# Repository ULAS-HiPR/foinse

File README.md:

# Foinse

Foinse is the power-source and monitoring node in [Ogma](https://sean-osullivan.com/projects/ogma/), the University of Limerick Aeronautics Society's modular avionics stack for high-powered rocketry.

## Role

- Generates and distributes the shared stack power rails.
- Measures battery and servo current.
- Reports power health over the 500 kbit/s CAN bus.
- Provides the stack's electrical entry point while each node performs its own local regulation.

## Repository

- `hardware/` - KiCad design and manufacturing outputs.
- `firmware/` - embedded firmware, power-path probes, and tests.

## Status

Rev 1 firmware and hardware bring-up continue on [`ogma/flight-hardening`](https://github.com/ULAS-HiPR/foinse/tree/ogma/flight-hardening). Release-candidate firmware builds and software tests pass, but hardware-in-the-loop validation is still underway. Foinse is not yet flight-proven.

## Manufacturing support

Rev 1 PCB fabrication was sponsored through [EasyEDA Education](https://easyeda.com/education) and manufactured by [JLCPCB](https://jlcpcb.com/). The board was designed in KiCad and imported into EasyEDA Pro for the sponsorship and manufacturing workflow.

## More information

See the [Ogma project write-up](https://sean-osullivan.com/projects/ogma/) for the complete stack, bring-up work, and current status.

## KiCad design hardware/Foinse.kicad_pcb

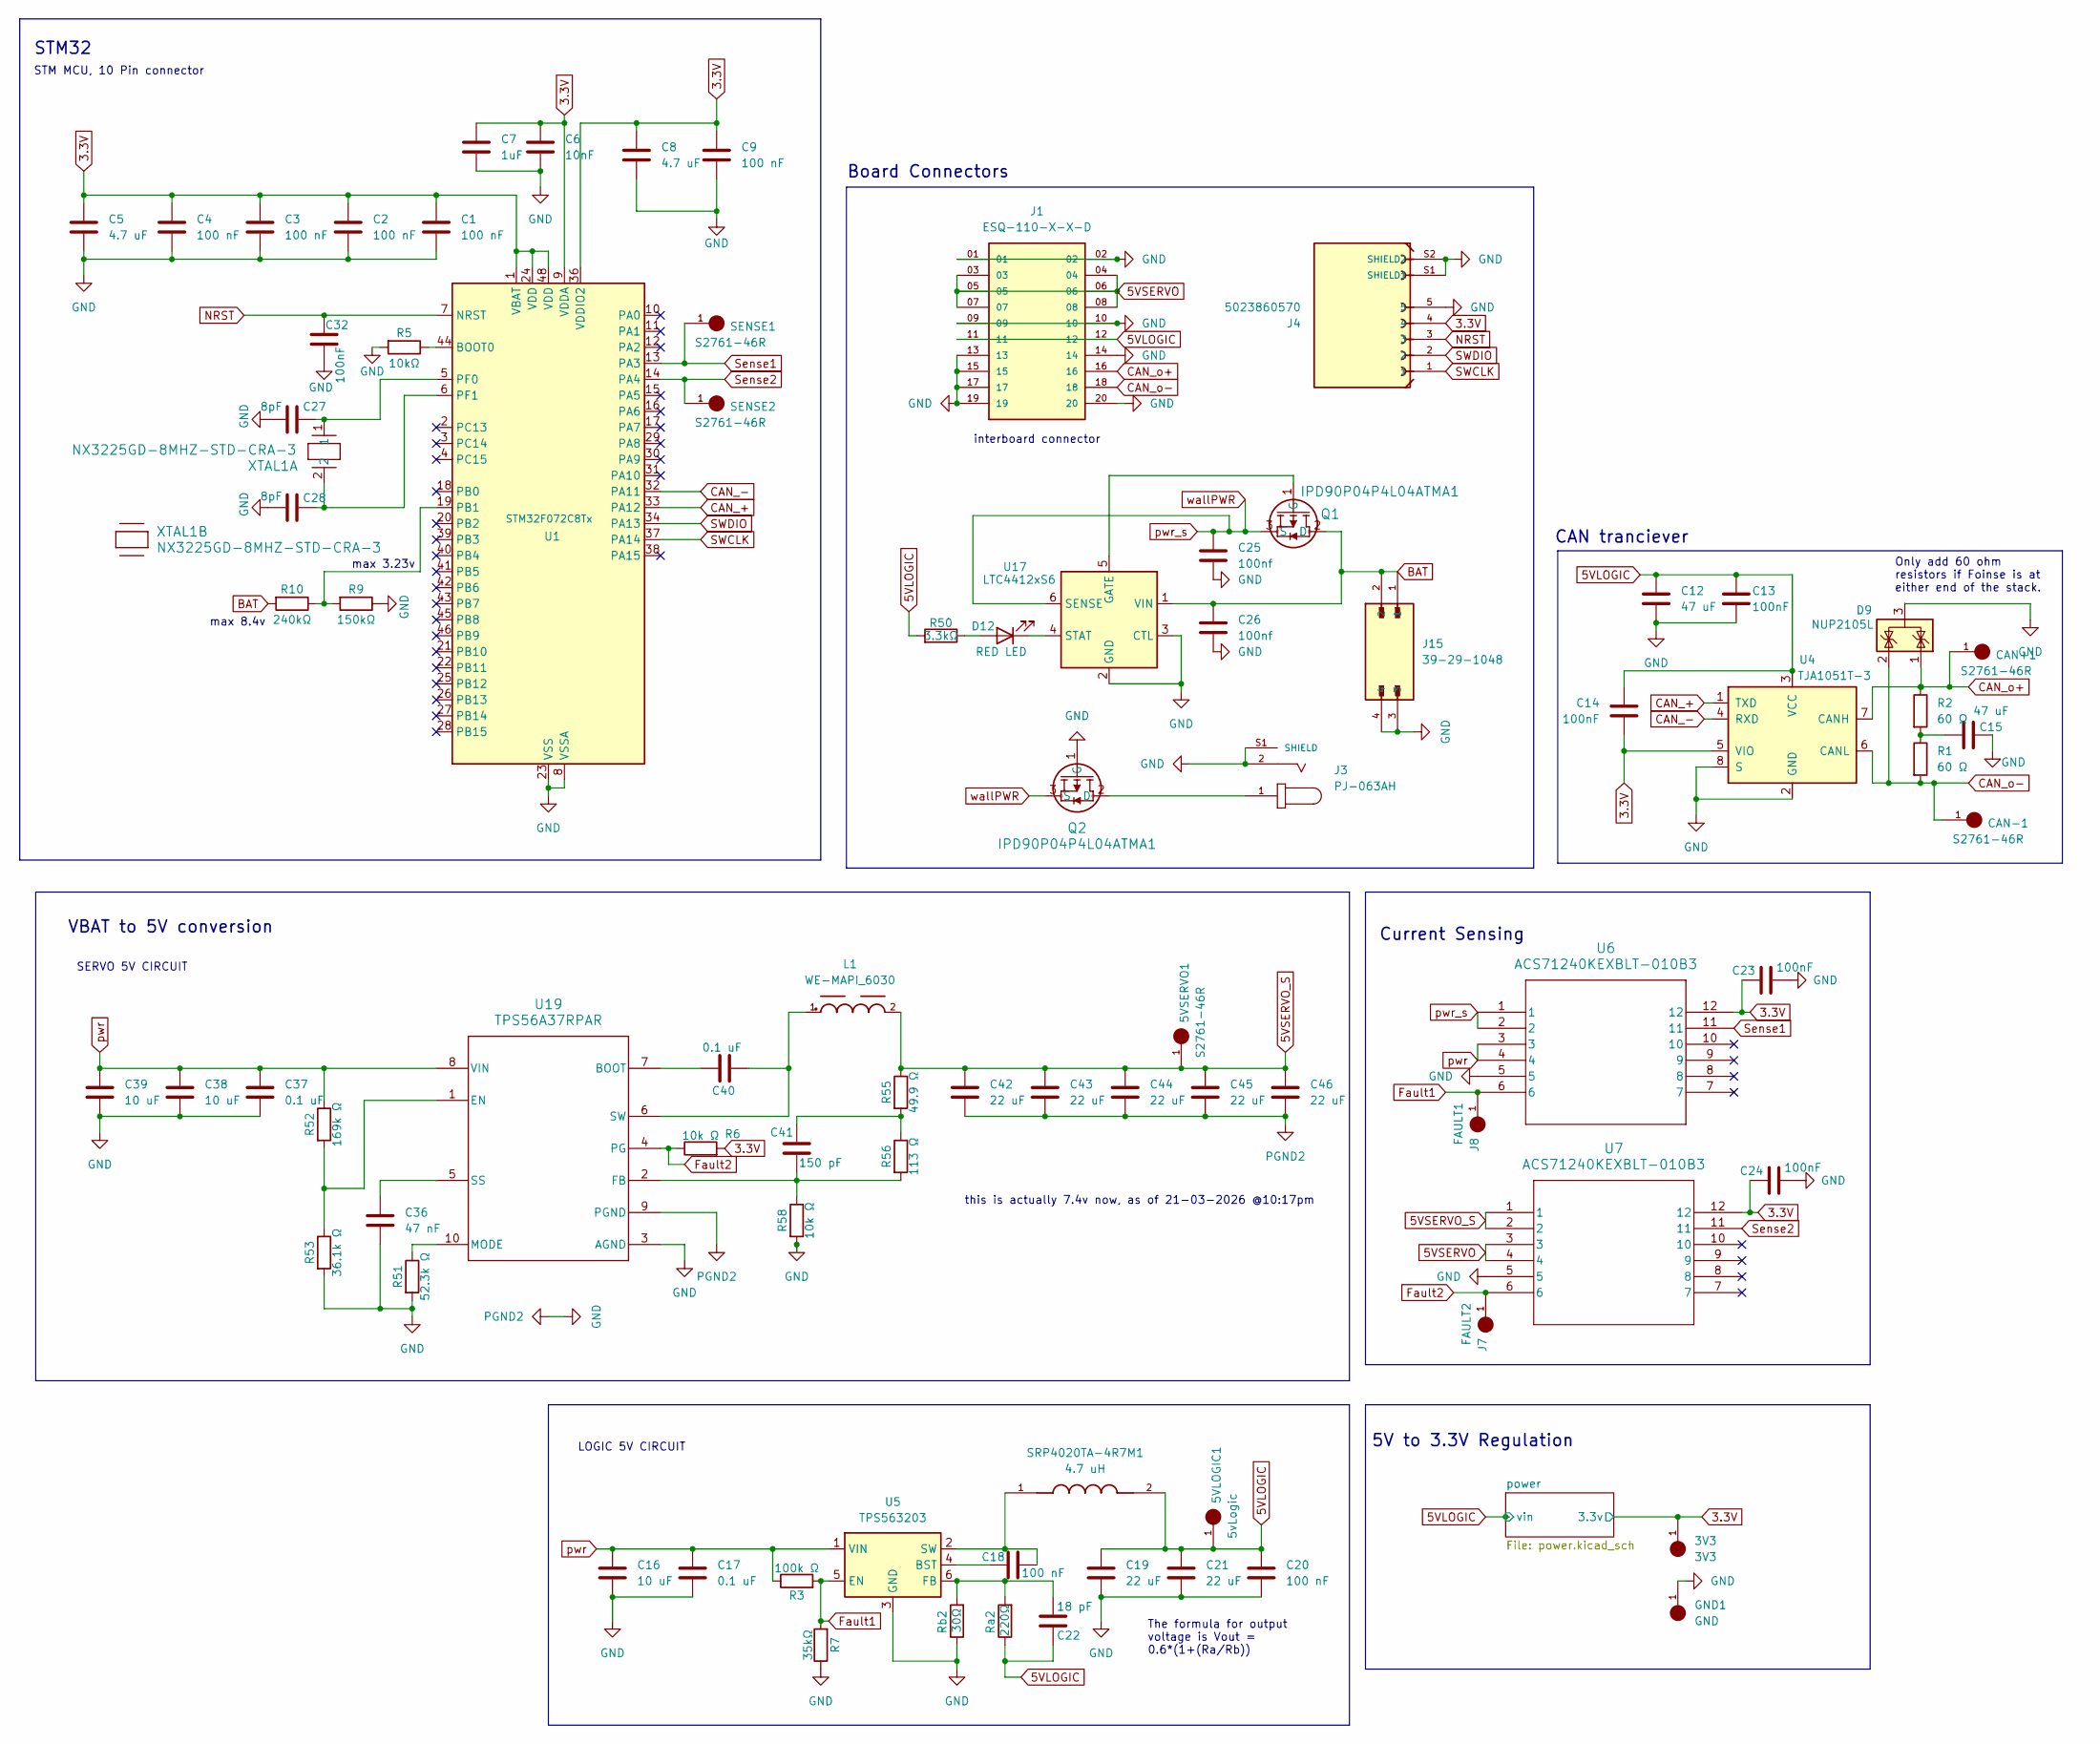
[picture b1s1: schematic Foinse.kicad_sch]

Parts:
3V3: 3V3; HARWIN_S2761-46R; PARTREV 1
5VLOGIC1: 5vLogic; HARWIN_S2761-46R; PARTREV 1
5VSERVO1: S2761-46R; HARWIN_S2761-46R; PARTREV 1
C1, C2, C3, C4, C9, C18, C20: 100 nF; C_0402_1005Metric
C5, C8: 4.7 uF; C_0402_1005Metric
C6: 10nF; C_0603_1608Metric
C7: 1uF; C_0402_1005Metric
C12, C15: 47 uF; C_0603_1608Metric
C13, C14, C23, C24, C32: 100nF; C_0402_1005Metric
C16, C38, C39: 10 uF; C_0603_1608Metric
C17, C37, C40: 0.1 uF; C_0402_1005Metric
C19, C21, C42, C43, C44, C45, C46: 22 uF; C_0603_1608Metric
C22: 18 pF; C_0402_1005Metric
C25, C26: 100nf; C_0402_1005Metric
C27, C28: 8pF; C_0402_1005Metric
C36: 47 nF; C_0402_1005Metric
C41: 150 pF; C_0402_1005Metric
CAN+1: S2761-46R; HARWIN_S2761-46R; PARTREV 1
CAN-1: S2761-46R; HARWIN_S2761-46R; PARTREV 1
D9: NUP2105L; SOT-23
D12: RED LED; LED_0402_1005Metric
GND1: GND; HARWIN_S2761-46R; PARTREV 1
J1: ESQ-110-X-X-D; SAMTEC_ESQ-110-14-G-D; PARTREV NA
J3: PJ-063AH; CUI_PJ-063AH; PARTREV 1.02
J4: 5023860570; MOLEX_5023860570; PARTREV F
J7: FAULT2; HARWIN_S2761-46R; PARTREV 1
J8: FAULT1; HARWIN_S2761-46R; PARTREV 1
J15: 39-29-1048; MOLEX_39-29-1048
L1: WE-MAPI_6030
Q1, Q2: IPD90P04P4L04ATMA1; PG-TO252-3-313_INF
R1, R2: 60 Ω; R_0402_1005Metric
R3: 100k Ω; R_0402_1005Metric
R5: 10kΩ; R_0402_1005Metric
R6, R58: 10k Ω; R_0402_1005Metric
R7: 35kΩ; R_0402_1005Metric
R9: 150kΩ; R_0402_1005Metric
R10: 240kΩ; R_0402_1005Metric
R50: 3.3kΩ; R_0402_1005Metric
R51: 52.3k Ω; R_0402_1005Metric
R52: 169k Ω; R_0402_1005Metric
R53: 36.1k Ω; R_0402_1005Metric
R55: 49.9 Ω; R_0402_1005Metric
R56: 113 Ω; R_0402_1005Metric
Ra2: 220Ω; R_0402_1005Metric
Rb2: 30Ω; R_0402_1005Metric
SENSE1, SENSE2: S2761-46R; HARWIN_S2761-46R; PARTREV 1
SRP4020TA-4R7M1: 4.7 uH; IND_SRP4020TA-4R7M
U1: STM32F072C8Tx; LQFP-48_7x7mm_P0.5mm
U4: TJA1051T-3; SOIC-8_3.9x4.9mm_P1.27mm
U5: TPS563203; SOT-563
U6, U7: ACS71240KEXBLT-010B3; QFN12_ACS711KEXLT-31AB-T_ALM
U17: LTC4412xS6; TSOT-23-6
U19: TPS56A37RPAR; RPA0010A-MFG
XTAL1: NX3225GD-8MHZ-STD-CRA-3; XTAL_NX3225GD-8MHZ-STD-CRA-3_NDK

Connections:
3.3V: 3V3.1, C1.1, C2.1, C3.1, C4.1, C5.1, C6.1, C7.1, C8.1, C9.1, C14.1, C23.2, C24.2, J4.4, R6.2, U1.1 (VBAT), U1.9 (VDDA), U1.24 (VDD), U1.36 (VDDIO2), U1.48 (VDD), U4.5 (VIO), U6.12, U7.12; also elsewhere on the board
5VLOGIC: 5VLOGIC1.1, C12.1, C13.1, C14.2, C19.1, C20.1, C21.1, C22.2, J1.11, J1.12, R50.2, Ra2.1, SRP4020TA-4R7M1.2, U4.3 (VCC); also elsewhere on the board
5VSERVO: J1.03, J1.04, J1.05, J1.06, J1.07, J1.08, U7.3, U7.4
5VSERVO_S: 5VSERVO1.1, C42.1, C43.1, C44.1, C45.1, C46.1, L1.2, R55.1, U7.1, U7.2; also elsewhere on the board
BAT: C26.1, J15.1, J15.2, Q1.2 (D), R10.2, U17.1 (VIN)
CAN_+: U1.33 (PA12), U4.1 (TXD)
CAN_-: U1.32 (PA11), U4.4 (RXD)
CAN_o+: CAN+1.1, D9.1 (K), J1.16, R2.1, U4.7 (CANH); also elsewhere on the board
CAN_o-: CAN-1.1, D9.2 (K), J1.18, R1.2, U4.6 (CANL); also elsewhere on the board
Fault1: J8.1, R3.2, R7.2, U5.5 (EN), U6.6; also elsewhere on the board
Fault2: J7.1, R6.1, U7.6, U19.4 (PG); also elsewhere on the board
GND: C1.2, C2.2, C3.2, C4.2, C5.2, C6.2, C7.2, C8.2, C9.2, C12.2, C13.2, C15.2, C16.2, C17.2, C19.2, C20.2, C21.2, C23.1, C24.1, C25.2, C26.2, C27.1, C28.2, C32.2, C36.2, C37.2, C38.2, C39.2, C42.2, C43.2, C44.2, C45.2, C46.2, D9.3 (A), GND1.1, J1.01, J1.02, J1.09, J1.10, J1.13, J1.14, J1.15, J1.17, J1.19, J1.20, J3.2, J3.S1 (SHIELD), J3.S2 (SHIELD), J4.5, J4.S1 (SHIELD1), J4.S2 (SHIELD2), J15.3, J15.4, Q2.1 (G), R5.2, R7.1, R9.1, R51.2, R53.2, R58.2, Rb2.1, U1.8 (VSSA), U1.23 (VSS), U1.35 (VSS), U1.47 (VSS), U4.2 (GND), U4.8 (S), U5.3 (GND), U6.5, U7.5, U17.2 (GND), U17.3 (CTL), U19.3 (AGND), U19.9 (PGND); also elsewhere on the board
NRST: C32.1, J4.3, U1.7 (NRST)
unnamed: C15.1, R1.1, R2.2
unnamed: C41.1, R55.2, R56.1
unnamed: D12.2 (A), R50.1
unnamed: D12.1 (K), U17.4 (STAT)
unnamed: Q1.1 (G), U17.5 (GATE)
unnamed: J3.1, Q2.2 (D)
unnamed: R5.1, U1.44 (BOOT0)
unnamed: R9.2, R10.1, U1.19 (PB1)
unnamed: C27.2, U1.5 (PF0), XTAL1.1
unnamed: C28.1, U1.6 (PF1), XTAL1.2
unnamed: C18.2, U5.4 (BST)
unnamed: C22.1, Ra2.2, Rb2.2, U5.6 (FB)
unnamed: C18.1, SRP4020TA-4R7M1.1, U5.2 (SW)
unnamed: C40.1, U19.7 (BOOT)
unnamed: R52.2, R53.1, U19.1 (EN)
unnamed: C41.2, R56.2, R58.1, U19.2 (FB)
unnamed: R51.1, U19.10 (MODE)
unnamed: C36.1, U19.5 (SS)
unnamed: C40.2, L1.1, U19.6 (SW)
SWCLK: J4.1, U1.37 (PA14)
SWDIO: J4.2, U1.34 (PA13)
Sense1: SENSE1.1, U1.13 (PA3), U6.11; also elsewhere on the board
Sense2: SENSE2.1, U1.14 (PA4), U7.11; also elsewhere on the board
pwr: C16.1, C17.1, C37.1, C38.1, C39.1, R3.1, R52.1, U5.1 (VIN), U6.3, U6.4, U19.8 (VIN)
pwr_s: C25.1, Q1.3 (S), Q2.3 (S), U6.1, U6.2, U17.6 (SENSE)

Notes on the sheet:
max 3.23v
Board Connectors
5V to 3.3V Regulation
Current Sensing
this is actually 7.4v now, as of 21-03-2026 @10:17pm
interboard connector
STM MCU, 10 Pin connector
STM32
max 8.4v
VBAT to 5V conversion
CAN tranciever
LOGIC 5V CIRCUIT
SERVO 5V CIRCUIT
Only add 60 ohm resistors if Foinse is at either end of the stack.
The formula for output voltage is Vout = 0.6*(1+(Ra/Rb))

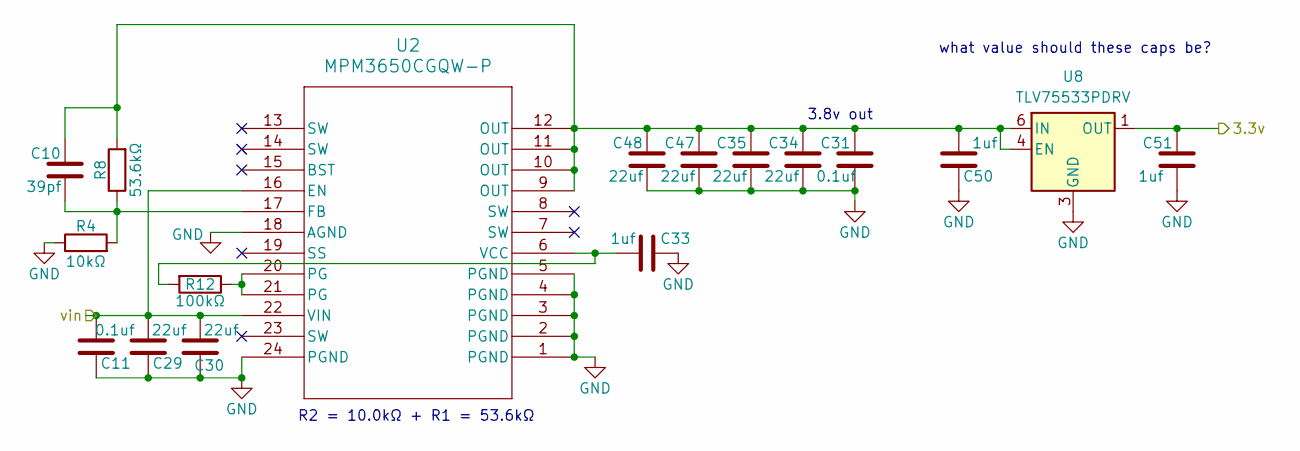
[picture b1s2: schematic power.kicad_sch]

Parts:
C10: 39pf; C_0402_1005Metric
C11, C31: 0.1uf; C_0402_1005Metric
C29, C30, C34, C35, C47, C48: 22uf; C_0603_1608Metric
C33, C50, C51: 1uf; C_0402_1005Metric
R4: 10kΩ; R_0402_1005Metric
R8: 53.6kΩ; R_0402_1005Metric
R12: 100kΩ; R_0402_1005Metric
U2: MPM3650CGQW-P; QFN-24_MPM3650_MNP
U8: TLV75533PDRV; WSON-6-1EP_2x2mm_P0.65mm_EP1x1.6mm

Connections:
3.3V: C51.1, U8.1 (OUT); also elsewhere on the board
5VLOGIC: C11.2, C29.2, C30.2, U2.16 (EN), U2.22 (VIN); also elsewhere on the board
GND: C11.1, C29.1, C30.1, C31.2, C33.1, C34.2, C35.2, C47.2, C48.2, C50.1, C51.2, R4.1, U2.1 (PGND), U2.2 (PGND), U2.3 (PGND), U2.4 (PGND), U2.5 (PGND), U2.18 (AGND), U2.24 (PGND), U8.3 (GND), U8.7 (GND); also elsewhere on the board
unnamed: R12.1, U2.20 (PG), U2.21 (PG)
unnamed: C10.2, R4.2, R8.1, U2.17 (FB)
unnamed: C33.2, R12.2, U2.6 (VCC)
unnamed: C10.1, C31.1, C34.1, C35.1, C47.1, C48.1, C50.2, R8.2, U2.9 (OUT), U2.10 (OUT), U2.11 (OUT), U2.12 (OUT), U8.4 (EN), U8.6 (IN)

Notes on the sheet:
R2 = 10.0kΩ + R1 = 53.6kΩ
3.8v out
what value should these caps be?

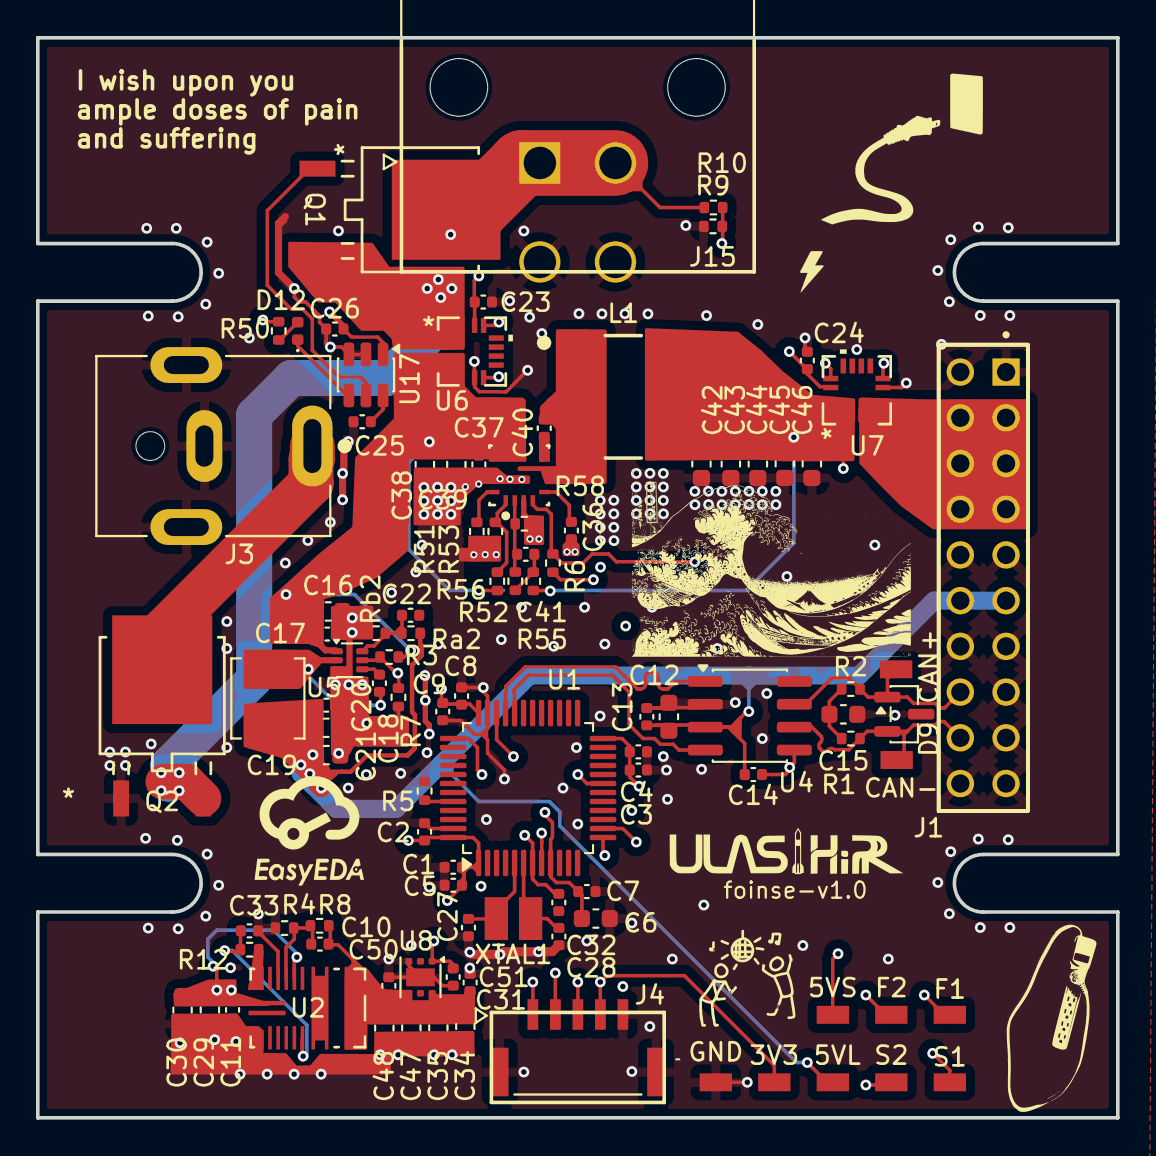
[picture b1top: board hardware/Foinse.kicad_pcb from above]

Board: 6 copper layers, 60.0 x 60.0 mm, 100 parts (0 on the bottom side), 42 nets.

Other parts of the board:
5VL: 5vLogic; HARWIN_S2761-46R
5VS: S2761-46R; HARWIN_S2761-46R
CAN+: S2761-46R; HARWIN_S2761-46R
CAN-: S2761-46R; HARWIN_S2761-46R
F1: FAULT1; HARWIN_S2761-46R
F2: FAULT2; HARWIN_S2761-46R
GND: GND; HARWIN_S2761-46R
S1, S2: S2761-46R; HARWIN_S2761-46R

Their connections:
5VLOGIC: 5VL.1; also elsewhere on the board
5VSERVO_S: 5VS.1; also elsewhere on the board
CAN_o+: CAN+.1; also elsewhere on the board
CAN_o-: CAN-.1; also elsewhere on the board
Fault1: F1.1; also elsewhere on the board
Fault2: F2.1; also elsewhere on the board
GND: GND.1; also elsewhere on the board
Sense1: S1.1; also elsewhere on the board
Sense2: S2.1; also elsewhere on the board

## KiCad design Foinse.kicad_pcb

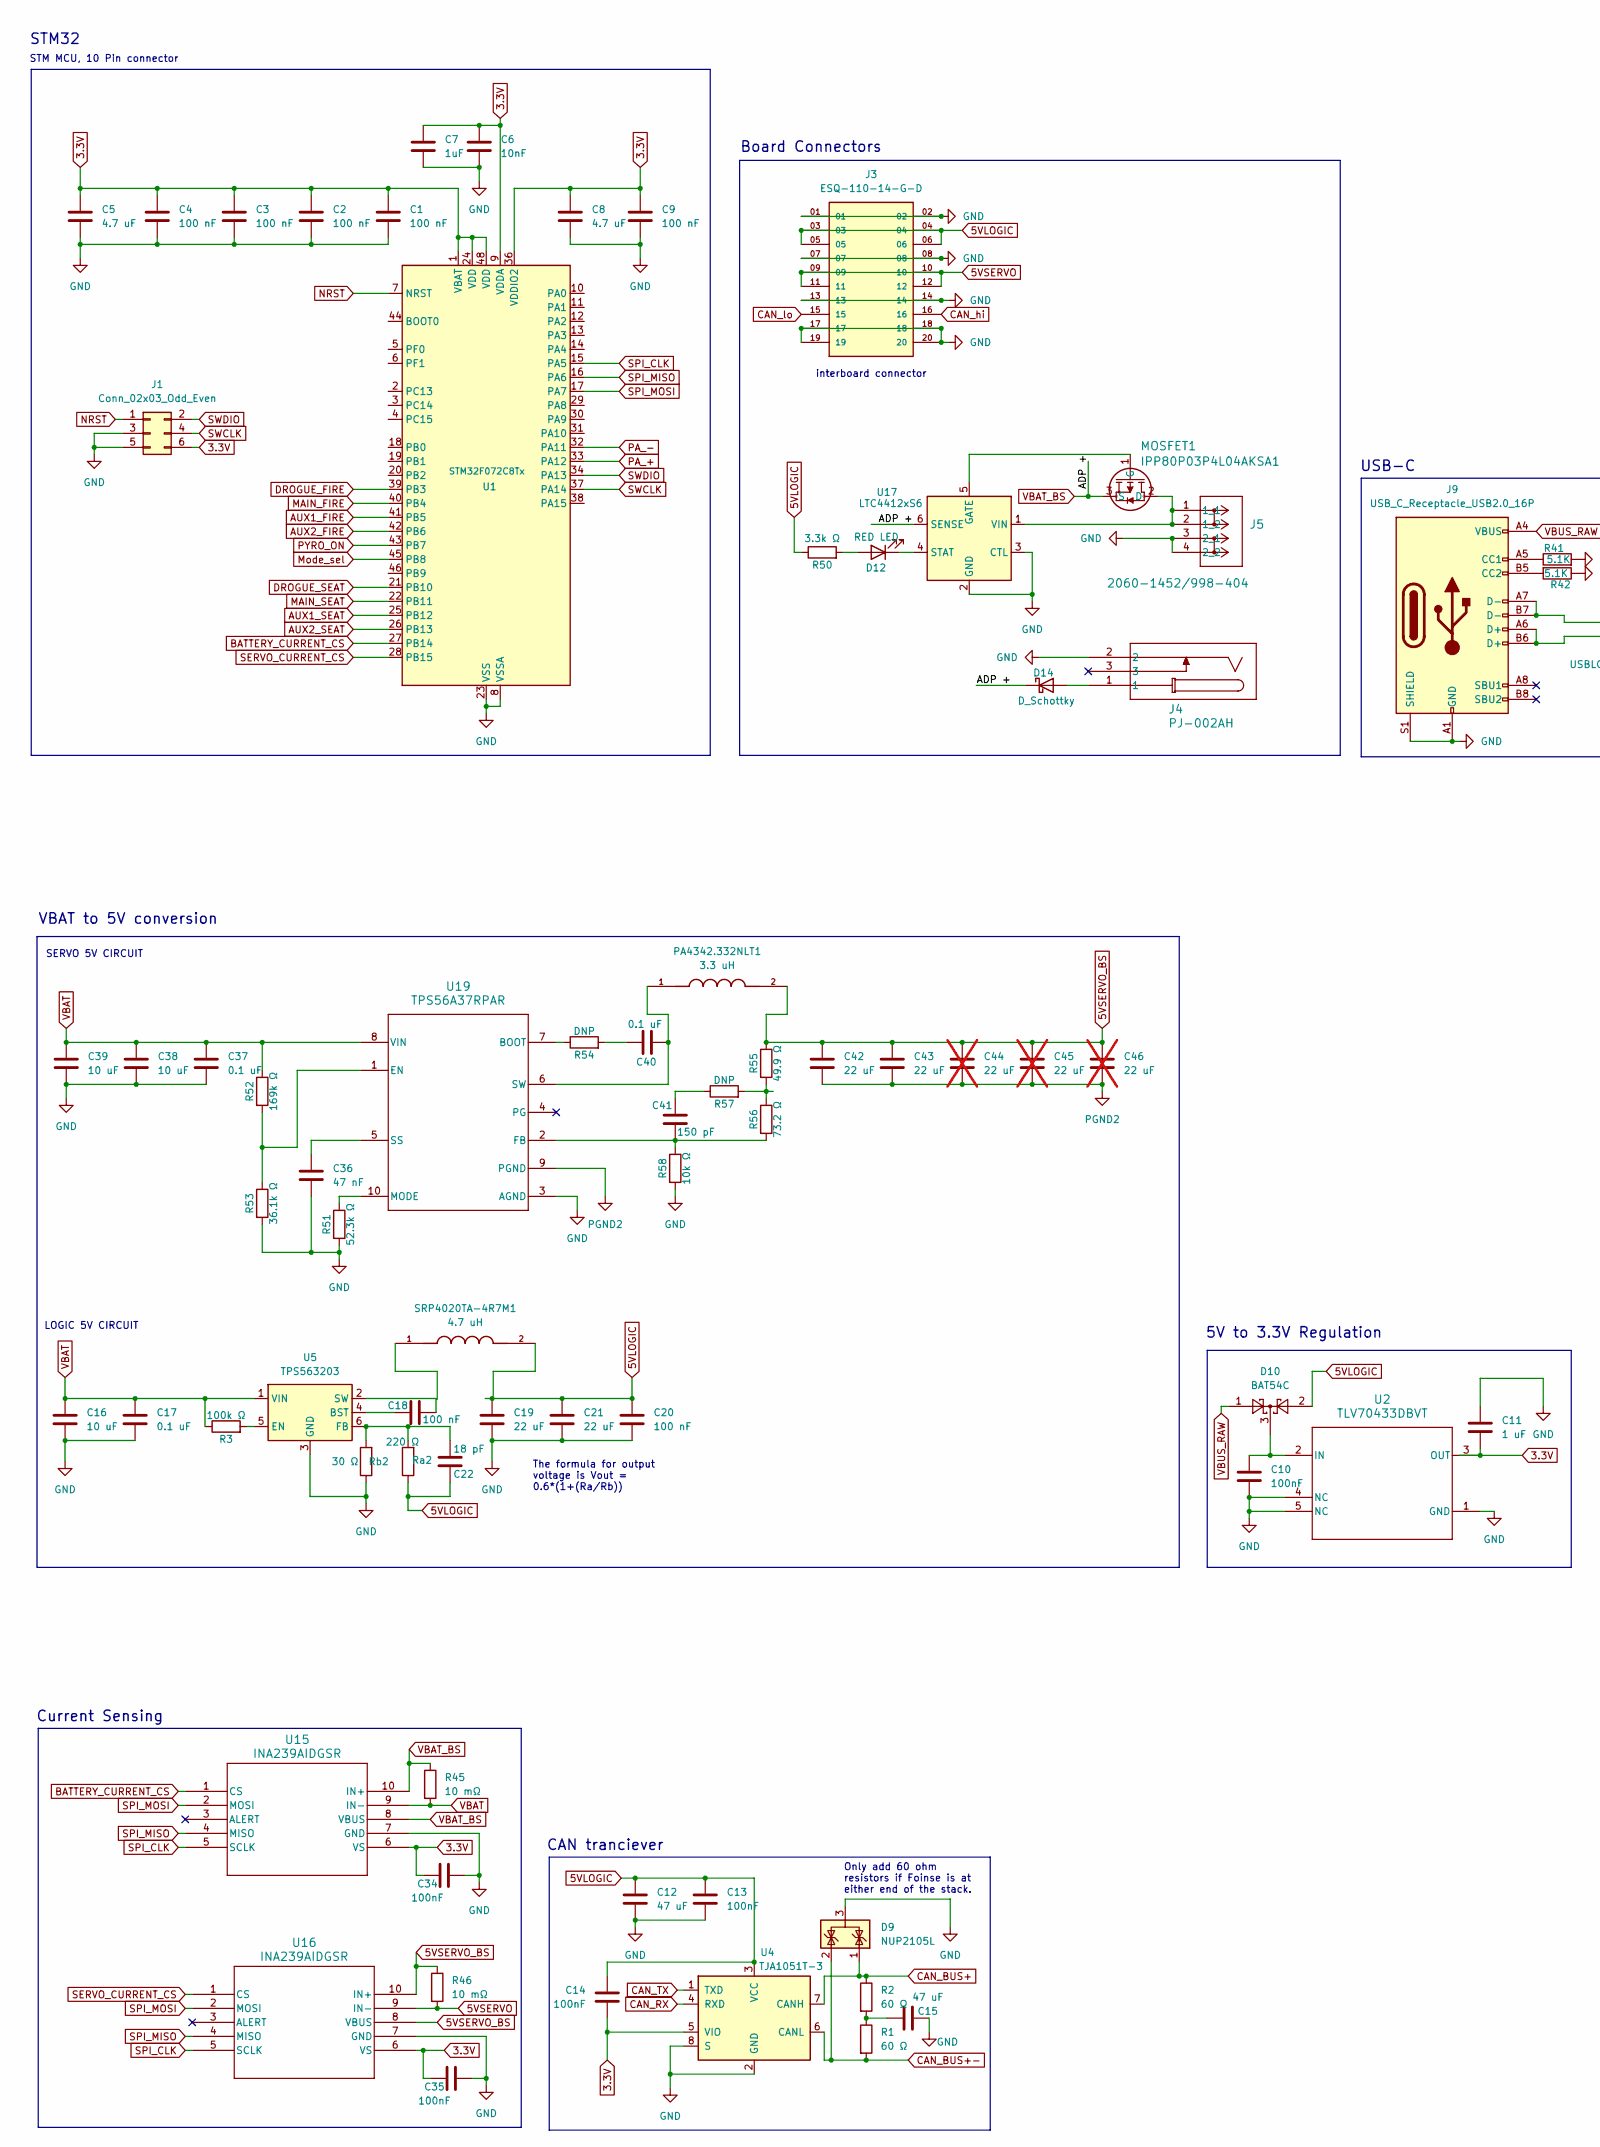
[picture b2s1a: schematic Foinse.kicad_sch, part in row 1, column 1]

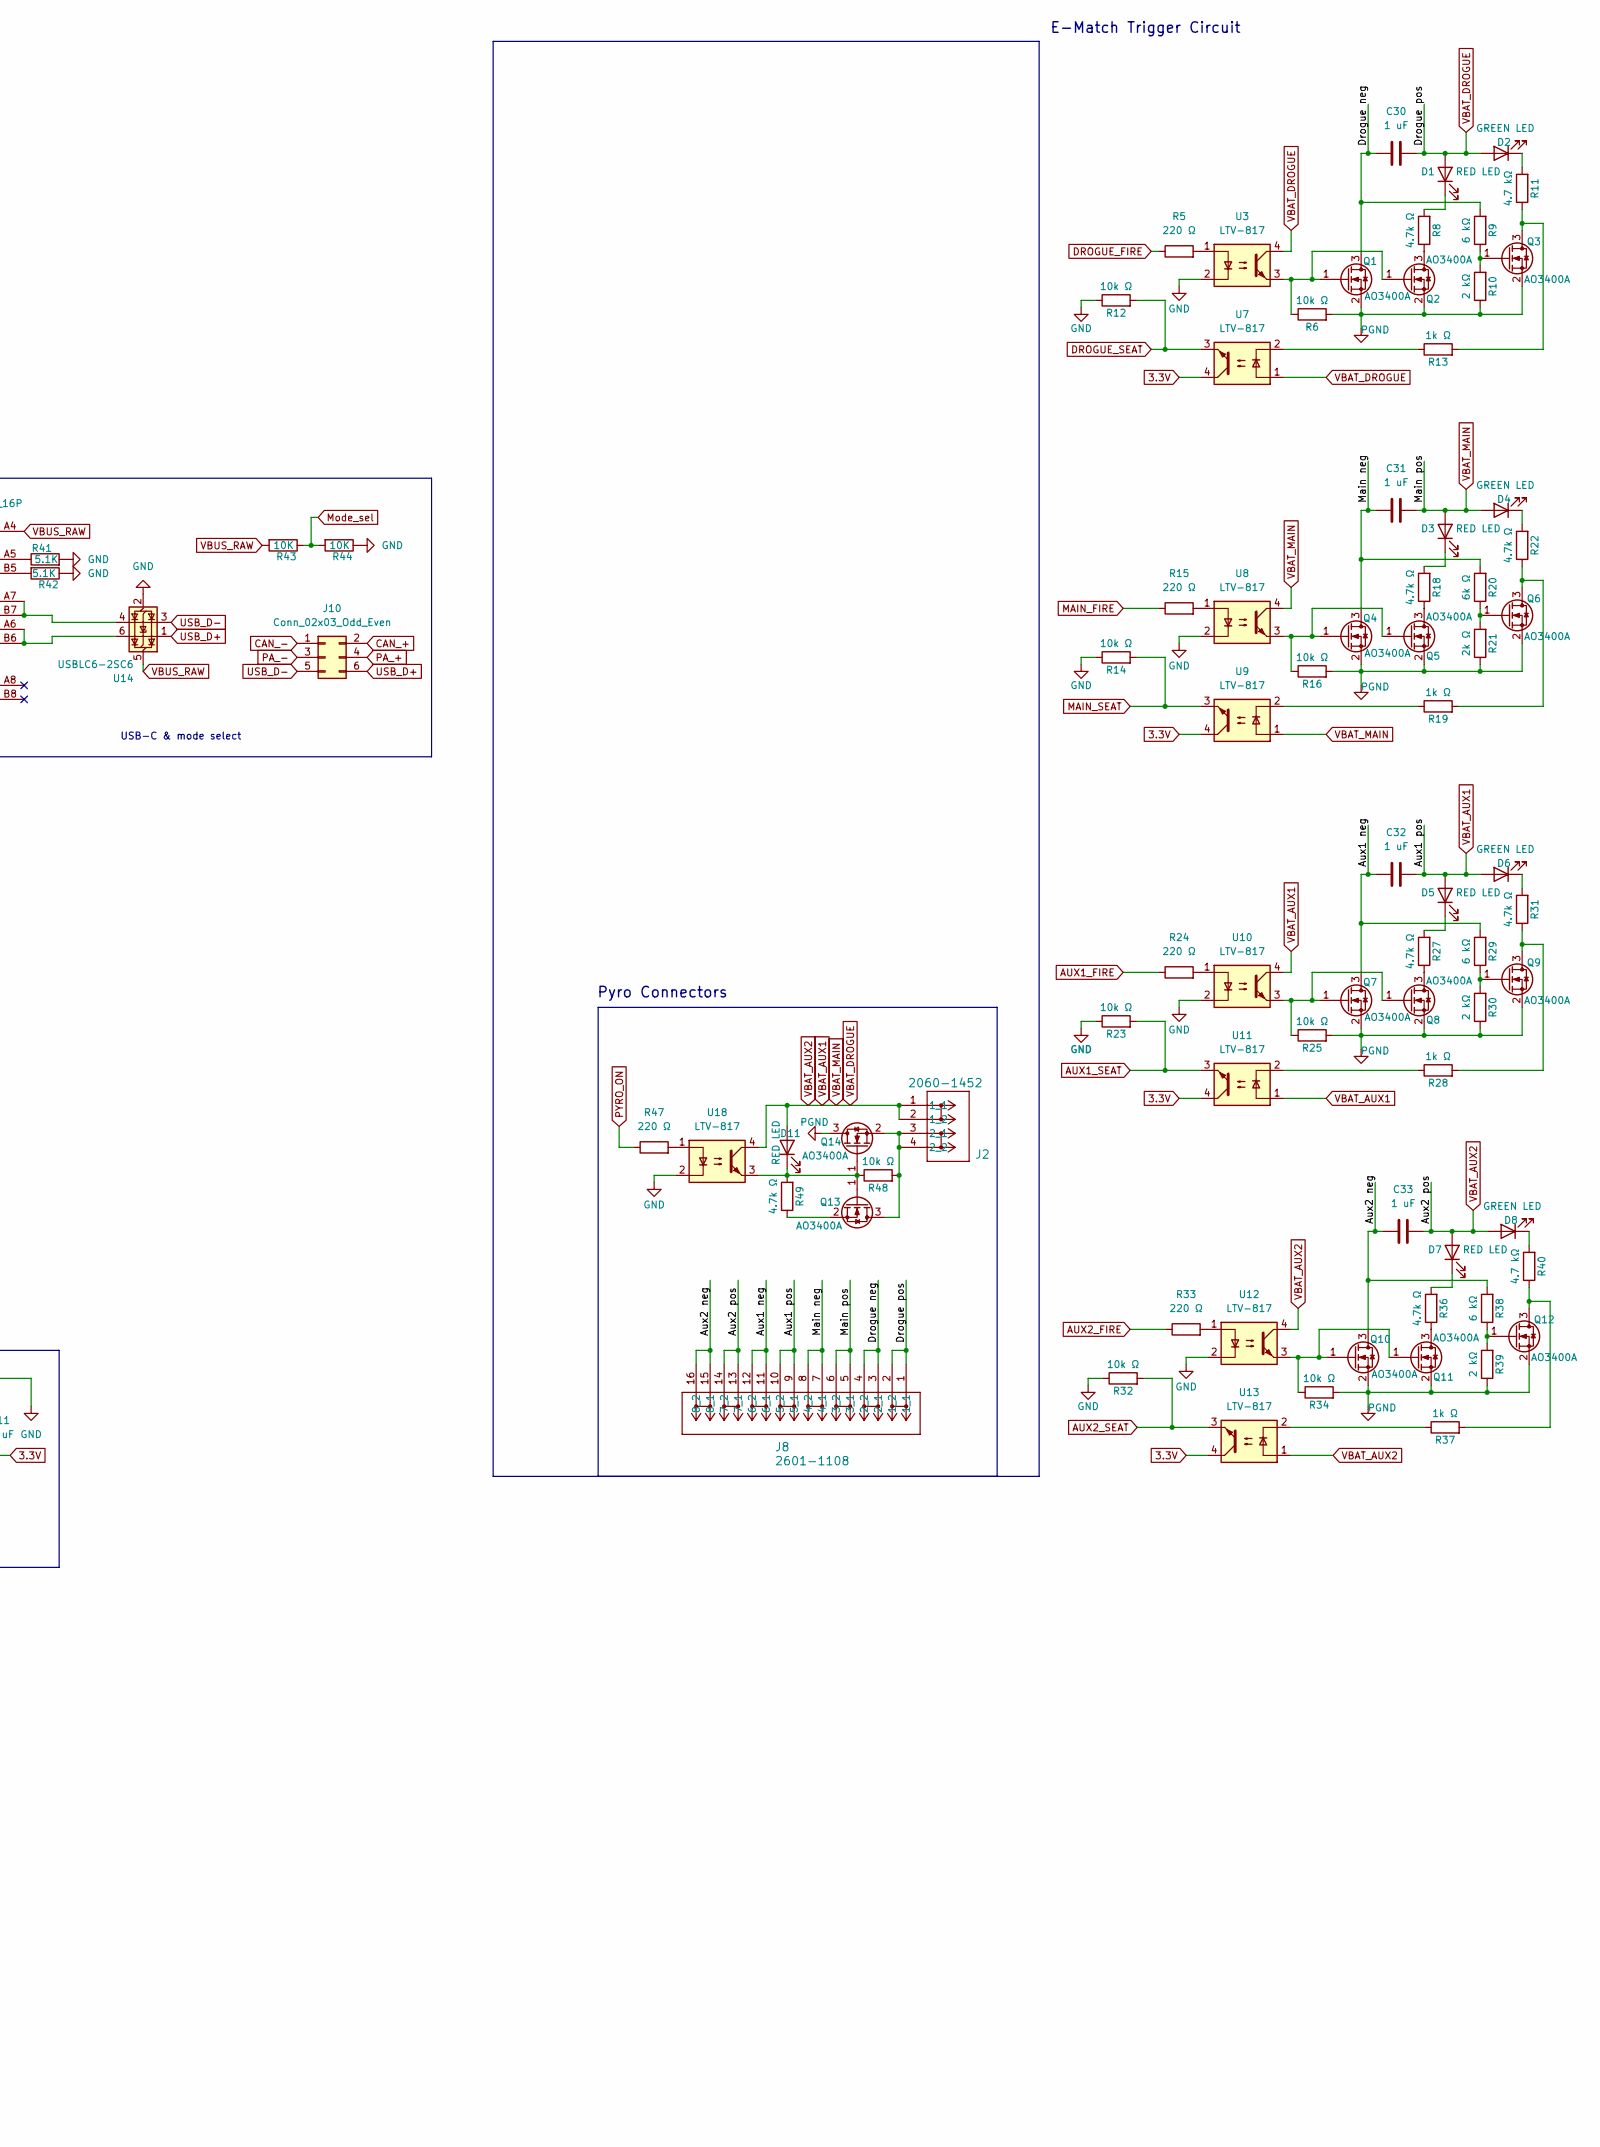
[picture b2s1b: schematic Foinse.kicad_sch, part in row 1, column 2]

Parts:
C1, C2, C3, C4, C9, C18, C20: 100 nF; C_0402_1005Metric
C5, C8: 4.7 uF; C_0402_1005Metric
C6: 10nF; C_0402_1005Metric
C7: 1uF; C_0402_1005Metric
C10, C13, C14, C34, C35: 100nF; C_0402_1005Metric
C11, C30, C31, C32, C33: 1 uF; C_0402_1005Metric
C12, C15: 47 uF; C_0402_1005Metric
C16, C38, C39: 10 uF; C_0402_1005Metric
C17, C37, C40: 0.1 uF; C_0402_1005Metric
C19, C21, C42, C43: 22 uF; C_0402_1005Metric
C22: 18 pF; C_0402_1005Metric
C36: 47 nF; C_0402_1005Metric
C41: 150 pF; C_0402_1005Metric
C44, C45, C46: 22 uF; C_0402_1005Metric; not fitted
D1, D3, D5, D7, D11, D12: RED LED; LED_0402_1005Metric
D2, D4, D6, D8: GREEN LED; LED_0402_1005Metric
D9: NUP2105L; SOT-23
D10: BAT54C; SOT-23
D14: D_Schottky; TO-220-3_Vertical
J1, J10: Conn_02x03_Odd_Even; PinHeader_2x03_P1.00mm_Vertical
J2: 2060-1452; WAG
J3: ESQ-110-14-G-D; SAMTEC_ESQ-110-14-G-D; PARTREV NA
J4: PJ-002AH; PJ-002AH_CUD
J5: 2060-1452/998-404; WAG
J8: 2601-1108; CONN8_2601-1108_WAG
J9: USB_C_Receptacle_USB2.0_16P; USB_C_Receptacle_G-Switch_GT-USB-7010ASV
MOSFET1: IPP80P03P4L04AKSA1
PA4342.332NLT1: 3.3 uH; IND_PA4342.332NLT; PARTREV P769.L (06/20)
Q1, Q2, Q3, Q4, Q5, Q6, Q7, Q8, Q9, Q10, Q11, Q12, Q13, Q14: AO3400A; SOT-23
R1, R2: 60 Ω; R_0402_1005Metric
R3: 100k Ω; R_0402_1005Metric
R5, R15, R24, R33, R47: 220 Ω; R_0402_1005Metric
R6, R12, R14, R16, R23, R25, R32, R34, R48, R58: 10k Ω; R_0402_1005Metric
R8, R18, R22, R27, R31, R36, R49: 4.7k Ω; R_0402_1005Metric
R9, R29, R38: 6 kΩ; R_0402_1005Metric
R10, R30, R39: 2 kΩ; R_0402_1005Metric
R11, R40: 4.7 kΩ; R_0402_1005Metric
R13, R19, R28, R37: 1k Ω; R_0402_1005Metric
R20: 6k Ω; R_0402_1005Metric
R21: 2k Ω; R_0402_1005Metric
R41, R42: 5.1K; R_0402_1005Metric
R43, R44: 10K; R_0402_1005Metric
R45, R46: 10 mΩ; R_0402_1005Metric
R50: 3.3k Ω; R_0402_1005Metric
R51: 52.3k Ω; R_0402_1005Metric
R52: 169k Ω; R_0402_1005Metric
R53: 36.1k Ω; R_0402_1005Metric
R54, R57: DNP; R_0402_1005Metric
R55: 49.9 Ω; R_0402_1005Metric
R56: 73.2 Ω; R_0402_1005Metric
Ra2: 220 Ω; R_0402_1005Metric
Rb2: 30 Ω; R_0402_1005Metric
SRP4020TA-4R7M1: 4.7 uH; IND_SRP4020TA-4R7M
U1: STM32F072C8Tx; LQFP-48_7x7mm_P0.5mm
U2: TLV70433DBVT; DBV0005A_N
U3, U7, U8, U9, U10, U11, U12, U13, U18: LTV-817; SO4_TOS
U4: TJA1051T-3; SOIC-8_3.9x4.9mm_P1.27mm
U5: TPS563203; SOT-563
U14: USBLC6-2SC6; SOT-23-6
U15, U16: INA239AIDGSR; VSSOP_9AIDGST_TEX
U17: LTC4412xS6; TSOT-23-6
U19: TPS56A37RPAR; RPA0010A-MFG

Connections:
3.3V: C1.1, C2.1, C3.1, C4.1, C5.1, C6.1, C7.1, C8.1, C9.1, C11.2, C14.1, C34.1, C35.1, J1.6, U1.1 (VBAT), U1.9 (VDDA), U1.24 (VDD), U1.36 (VDDIO2), U1.48 (VDD), U2.3 (OUT), U4.5 (VIO), U7.4, U9.4, U11.4, U13.4, U15.6 (VS), U16.6 (VS)
5VLOGIC: C12.1, C13.1, C14.2, C19.1, C20.1, C21.1, C22.2, D10.2, J3.03, J3.04, J3.05, J3.06, R50.1, Ra2.1, U4.3 (VCC)
5VSERVO: J3.09, J3.10, J3.11, J3.12, R46.2, U16.9 (IN-)
5VSERVO_BS: C42.1, C43.1, C44.1, C45.1, C46.1, PA4342.332NLT1.2, R46.1, R55.1, U16.8 (VBUS), U16.10 (IN+)
/Aux1 neg: C32.2, J8.11 (6_1), J8.12 (6_2), Q7.3 (D), R29.2
/Aux2 neg: C33.2, J8.15 (8_1), J8.16 (8_2), Q10.3 (D), R38.2
/Drogue neg: C30.2, J8.3 (2_1), J8.4 (2_2), Q1.3 (D), R9.2
/Main neg: C31.2, J8.7 (4_1), J8.8 (4_2), Q4.3 (D), R20.2
AUX1_FIRE: R24.1, U1.41 (PB5)
AUX1_SEAT: R23.2, U1.25 (PB12), U11.3
AUX2_FIRE: R33.1, U1.42 (PB6)
AUX2_SEAT: R32.2, U1.26 (PB13), U13.3
BATTERY_CURRENT_CS: U1.27 (PB14), U15.1 (CS)
CAN_+: J10.2
CAN_-: J10.1
CAN_BUS+: D9.1 (K), R2.1, U4.7 (CANH)
CAN_BUS+-: D9.2 (K), R1.2, U4.6 (CANL)
CAN_RX: U4.4 (RXD)
CAN_TX: U4.1 (TXD)
CAN_hi: J3.16
CAN_lo: J3.15
DROGUE_FIRE: R5.1, U1.39 (PB3)
DROGUE_SEAT: R12.2, U1.21 (PB10), U7.3
GND: C1.2, C2.2, C3.2, C4.2, C5.2, C6.2, C7.2, C8.2, C9.2, C10.2, C11.1, C12.2, C13.2, C15.2, C16.2, C17.2, C19.2, C20.2, C21.2, C34.2, C35.2, C36.2, C37.2, C38.2, C39.2, D9.3 (A), J1.3, J1.5, J3.01, J3.02, J3.07, J3.08, J3.13, J3.14, J3.17, J3.18, J3.19, J3.20, J4.2, J5.3 (2_1), J5.4 (2_2), J9.A1 (GND), J9.A12 (GND), J9.B1 (GND), J9.B12 (GND), J9.S1 (SHIELD), R12.1, R14.1, R23.1, R32.1, R41.2, R42.1, R44.1, R51.2, R53.2, R58.2, Rb2.1, U1.8 (VSSA), U1.23 (VSS), U1.35 (VSS), U1.47 (VSS), U2.1 (GND), U2.4 (NC), U2.5 (NC), U3.2, U4.2 (GND), U4.8 (S), U5.3 (GND), U8.2, U10.2, U12.2, U14.2 (GND), U15.7 (GND), U16.7 (GND), U17.2 (GND), U17.3 (CTL), U18.2, U19.3 (AGND)
MAIN_FIRE: R15.1, U1.40 (PB4)
MAIN_SEAT: R14.2, U1.22 (PB11), U9.3
Mode_sel: R43.1, R44.2, U1.45 (PB8)
NRST: J1.1, U1.7 (NRST)
unnamed: C15.1, R1.1, R2.2
unnamed: C40.1, R54.2
unnamed: C41.1, R57.1
unnamed: D1.1 (K), R8.2
unnamed: D2.1 (K), R11.2
unnamed: D3.1 (K), R18.2
unnamed: D4.1 (K), R22.2
unnamed: D5.1 (K), R27.2
unnamed: D6.1 (K), R31.2
unnamed: D7.1 (K), R36.2
unnamed: D8.1 (K), R40.2
unnamed: D11.1 (K), Q13.1 (G), Q14.1 (G), R48.1, R49.2, U18.3
unnamed: D12.2 (A), R50.2
unnamed: D12.1 (K), U17.4 (STAT)
unnamed: D14.2 (A), J4.1
unnamed: J2.3 (2_1), J2.4 (2_2), Q13.3 (D), Q14.2 (S), R48.2
unnamed: J5.1 (1_1), J5.2 (1_2), MOSFET1.2 (D), U17.1 (VIN)
unnamed: J9.A5 (CC1), R41.1
unnamed: J9.B5 (CC2), R42.2
unnamed: J9.A6 (D+), J9.B6 (D+), U14.6 (I/O1)
unnamed: J9.A7 (D-), J9.B7 (D-), U14.4 (I/O2)
unnamed: MOSFET1.1 (G), U17.5 (GATE)
unnamed: Q1.1 (G), Q2.1 (G), R6.1, U3.3
unnamed: Q2.3 (D), R8.1
unnamed: Q3.3 (D), R11.1, R13.2
unnamed: Q3.1 (G), R9.1, R10.2
unnamed: Q4.1 (G), Q5.1 (G), R16.1, U8.3
unnamed: Q5.3 (D), R18.1
unnamed: Q6.3 (D), R19.2, R22.1
unnamed: Q6.1 (G), R20.1, R21.2
unnamed: Q7.1 (G), Q8.1 (G), R25.1, U10.3
unnamed: Q8.3 (D), R27.1
unnamed: Q9.3 (D), R28.2, R31.1
unnamed: Q9.1 (G), R29.1, R30.2
unnamed: Q10.1 (G), Q11.1 (G), R34.1, U12.3
unnamed: Q11.3 (D), R36.1
unnamed: Q12.3 (D), R37.2, R40.1
unnamed: Q12.1 (G), R38.1, R39.2
unnamed: Q13.2 (S), R49.1
unnamed: R5.2, U3.1
unnamed: R13.1, U7.2
unnamed: R15.2, U8.1
unnamed: R19.1, U9.2
unnamed: R24.2, U10.1
unnamed: R28.1, U11.2
unnamed: R33.2, U12.1
unnamed: R37.1, U13.2
unnamed: R47.2, U18.1
unnamed: R55.2, R56.1, R57.2
unnamed: C10.1, D10.3, U2.2 (IN)
unnamed: C18.2, U5.4 (BST)
unnamed: R3.2, U5.5 (EN)
unnamed: C22.1, Ra2.2, Rb2.2, U5.6 (FB)
unnamed: C18.1, U5.2 (SW)
unnamed: R54.1, U19.7 (BOOT)
unnamed: R52.2, R53.1, U19.1 (EN)
unnamed: C41.2, R56.2, R58.1, U19.2 (FB)
unnamed: R51.1, U19.10 (MODE)
unnamed: C36.1, U19.5 (SS)
unnamed: C40.2, PA4342.332NLT1.1, U19.6 (SW)
PA_+: J10.4, U1.33 (PA12)
PA_-: J10.3, U1.32 (PA11)
PGND: Q1.2 (S), Q2.2 (S), Q3.2 (S), Q4.2 (S), Q5.2 (S), Q6.2 (S), Q7.2 (S), Q8.2 (S), Q9.2 (S), Q10.2 (S), Q11.2 (S), Q12.2 (S), Q14.3 (D), R6.2, R10.1, R16.2, R21.1, R25.2, R30.1, R34.2, R39.1
PGND2: C42.2, C43.2, C44.2, C45.2, C46.2, U19.9 (PGND)
PYRO_ON: R47.1, U1.43 (PB7)
SERVO_CURRENT_CS: U1.28 (PB15), U16.1 (CS)
SPI_CLK: U1.15 (PA5), U15.5 (SCLK), U16.5 (SCLK)
SPI_MISO: U1.16 (PA6), U15.4 (MISO), U16.4 (MISO)
SPI_MOSI: U1.17 (PA7), U15.2 (MOSI), U16.2 (MOSI)
SWCLK: J1.4, U1.37 (PA14)
SWDIO: J1.2, U1.34 (PA13)
USB_D+: J10.6, U14.1 (I/O1)
USB_D-: J10.5, U14.3 (I/O2)
VBAT: C16.1, C17.1, C37.1, C38.1, C39.1, R3.1, R45.2, R52.1, U5.1 (VIN), U15.9 (IN-), U19.8 (VIN)
VBAT_AUX1: C30.1, C31.1, C32.1, C33.1, D1.2 (A), D2.2 (A), D3.2 (A), D4.2 (A), D5.2 (A), D6.2 (A), D7.2 (A), D8.2 (A), D11.2 (A), J2.1 (1_1), J2.2 (1_2), J8.1 (1_1), J8.2 (1_2), J8.5 (3_1), J8.6 (3_2), J8.9 (5_1), J8.10 (5_2), J8.13 (7_1), J8.14 (7_2), U3.4, U7.1, U8.4, U9.1, U10.4, U11.1, U12.4, U13.1, U18.4
VBAT_BS: D14.1 (K), MOSFET1.3 (S), R45.1, U15.8 (VBUS), U15.10 (IN+), U17.6 (SENSE)
VBUS_RAW: D10.1, J9.A4 (VBUS), J9.A9 (VBUS), J9.B4 (VBUS), J9.B9 (VBUS), R43.2, U14.5 (VBUS)

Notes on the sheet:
Board Connectors
Pyro Connectors
E-Match Trigger Circuit
interboard connector
5V to 3.3V Regulation
Current Sensing
STM MCU, 10 Pin connector
STM32
USB-C & mode select
USB-C
VBAT to 5V conversion
CAN tranciever
LOGIC 5V CIRCUIT
SERVO 5V CIRCUIT
Only add 60 ohm resistors if Foinse is at either end of the stack.
The formula for output voltage is Vout = 0.6*(1+(Ra/Rb))
